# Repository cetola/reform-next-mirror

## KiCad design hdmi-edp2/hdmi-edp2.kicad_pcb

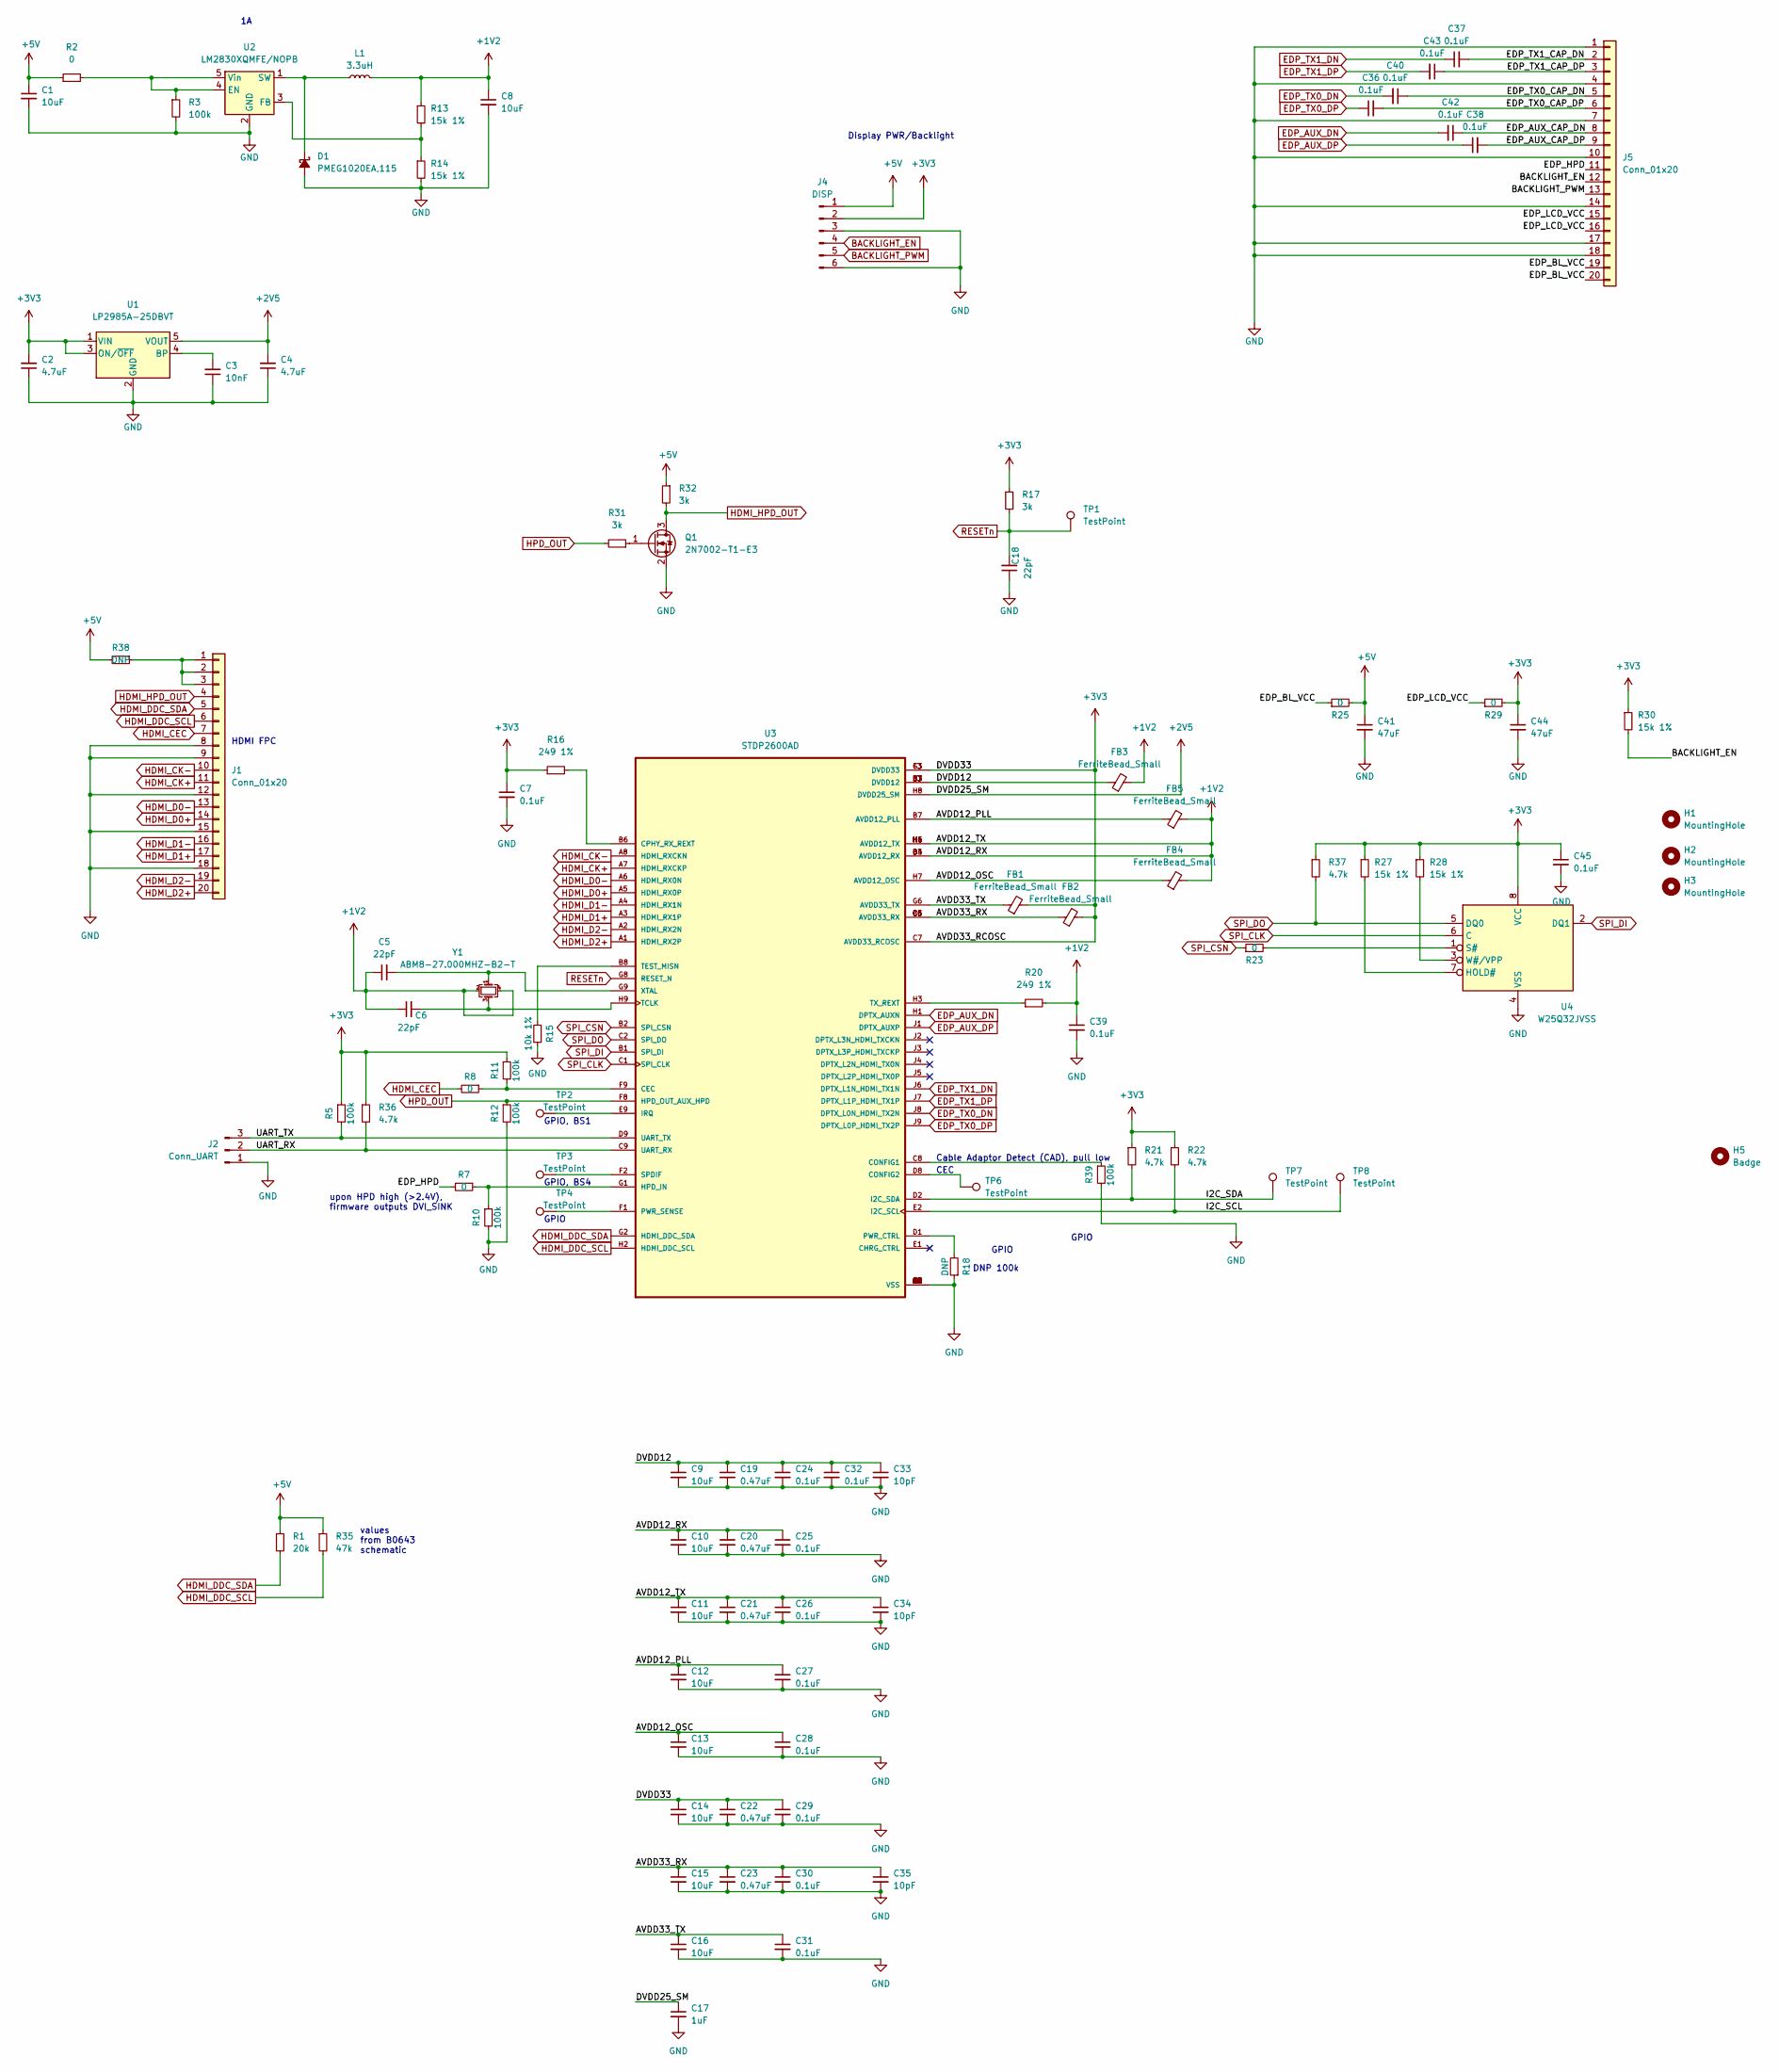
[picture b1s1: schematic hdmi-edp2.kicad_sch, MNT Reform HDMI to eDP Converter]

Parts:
C1, C8: 10uF; C_0603_1608Metric
C2, C4: 4.7uF; C_0402_1005Metric
C3: 10nF; C_0402_1005Metric
C5, C6, C18: 22pF; C_0402_1005Metric
C7, C24, C25, C26, C27, C28, C29, C30, C31, C32, C36, C37, C38, C39, C40, C42, C43, C45: 0.1uF; C_0402_1005Metric
C9, C10, C11, C12, C13, C14, C15, C16: 10uF; C_0402_1005Metric
C17: 1uF; C_0402_1005Metric
C19, C20, C21, C22, C23: 0.47uF; C_0402_1005Metric
C33, C34, C35: 10pF; C_0402_1005Metric
C41, C44: 47uF; C_0805_2012Metric
D1: PMEG1020EA,115; D_SOD-323
FB1, FB2, FB3, FB4, FB5: FerriteBead_Small; R_0603_1608Metric
H1, H2, H3: MountingHole; MountingHole_2.2mm_M2
H5: Badge; mnt-rhdp-badge-d1
J1: Conn_01x20; Hirose_FH12-20S-0.5SH_1x20-1MP_P0.50mm_Horizontal
J2: Conn_UART; PinHeader_1x03_P2.54mm_Vertical
J4: DISP; JST_SH_SM06B-SRSS-TB_1x06-1MP_P1.00mm_Horizontal
J5: Conn_01x20; JST_SH_SM20B-SRSS-TB_1x20-1MP_P1.00mm_Horizontal
L1: 3.3uH; L_1210_3225Metric
Q1: 2N7002-T1-E3; SOT-23
R1: 20k; R_0603_1608Metric
R2, R7, R8, R23, R25, R29: 0; R_0603_1608Metric
R3, R5, R10, R11, R12, R39: 100k; R_0603_1608Metric
R13, R14, R27, R28, R30: 15k 1%; R_0603_1608Metric
R15: 10k 1%; R_0603_1608Metric
R16, R20: 249 1%; R_0603_1608Metric
R17, R31, R32: 3k; R_0603_1608Metric
R18, R38: DNP; R_0603_1608Metric
R21, R22, R36, R37: 4.7k; R_0603_1608Metric
R35: 47k; R_0603_1608Metric
TP1, TP2, TP3, TP4, TP6, TP7, TP8: TestPoint; TestPoint_Pad_D1.0mm
U1: LP2985A-25DBVT; SOT-23-5
U2: LM2830XQMFE/NOPB; SOT-23-5
U3: STDP2600AD; BGA81C80P9X9_800X800X140N
U4: W25Q32JVSS; SOIC-8W_5.3x5.3mm_P1.27mm
Y1: ABM8-27.000MHZ-B2-T; Crystal_SMD_3225-4Pin_3.2x2.5mm

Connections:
+1V2: C5.1, C6.1, C8.1, C10.1, C11.1, C20.1, C21.1, C25.1, C26.1, C34.1, C39.1, FB3.2, FB4.2, FB5.2, L1.2, R13.1, R20.2, U3.B3 (AVDD12_RX), U3.B4 (AVDD12_RX), U3.H4 (AVDD12_TX), U3.H5 (AVDD12_TX), U3.H6 (AVDD12_TX), Y1.2, Y1.4
+2V5: C4.2, C17.1, U1.5 (VOUT), U3.H8 (DVDD25_SM)
+3V3: C2.2, C7.1, C14.1, C22.1, C29.1, C44.1, C45.1, FB1.2, FB2.2, J4.2, R5.1, R11.1, R16.1, R17.1, R21.1, R22.1, R27.1, R28.1, R29.2, R30.1, R36.1, R37.1, U1.1 (VIN), U1.3 (ON/~OFF), U3.C7 (AVDD33_RCOSC), U3.F3 (DVDD33), U3.G3 (DVDD33), U4.8 (VCC)
+5V: C1.1, C41.1, J4.1, R1.1, R2.1, R25.2, R32.1, R35.1, R38.2
/AVDD12_OSC: C13.1, C28.1, FB4.1, U3.H7 (AVDD12_OSC)
/AVDD12_PLL: C12.1, C27.1, FB5.1, U3.B7 (AVDD12_PLL)
/AVDD33_RX: C15.1, C23.1, C30.1, C35.1, FB2.1, U3.B5 (AVDD33_RX), U3.C5 (AVDD33_RX), U3.C6 (AVDD33_RX)
/AVDD33_TX: C16.1, C31.1, FB1.1, U3.G6 (AVDD33_TX)
/DVDD12: C9.1, C19.1, C24.1, C32.1, C33.1, FB3.1, U3.D3 (DVDD12), U3.D7 (DVDD12), U3.E3 (DVDD12), U3.E7 (DVDD12)
/EDP_AUX_CAP_DN: C42.1, J5.8
/EDP_AUX_CAP_DP: C38.2, J5.9
/EDP_BL_VCC: J5.19, J5.20, R25.1
/EDP_HPD: J5.11, R7.2
/EDP_LCD_VCC: J5.15, J5.16, R29.1
/EDP_TX0_CAP_DN: C40.1, J5.5
/EDP_TX0_CAP_DP: C36.2, J5.6
/EDP_TX1_CAP_DN: C37.2, J5.2
/EDP_TX1_CAP_DP: C43.1, J5.3
/I2C_SCL: R22.2, TP8.1, U3.E2 (I2C_SCL)
/I2C_SDA: R21.2, TP7.1, U3.D2 (I2C_SDA)
/UART_RX: J2.2, R36.2, U3.C9 (UART_RX)
/UART_TX: J2.3, R5.2, U3.D9 (UART_TX)
BACKLIGHT_EN: J4.4, J5.12, R30.2
BACKLIGHT_PWM: J4.5, J5.13
EDP_AUX_DN: C42.2, U3.H1 (DPTX_AUXN)
EDP_AUX_DP: C38.1, U3.J1 (DPTX_AUXP)
EDP_TX0_DN: C40.2, U3.J8 (DPTX_L0N_HDMI_TX2N)
EDP_TX0_DP: C36.1, U3.J9 (DPTX_L0P_HDMI_TX2P)
EDP_TX1_DN: C37.1, U3.J6 (DPTX_L1N_HDMI_TX1N)
EDP_TX1_DP: C43.2, U3.J7 (DPTX_L1P_HDMI_TX1P)
GND: C1.2, C2.1, C3.1, C4.1, C7.2, C8.2, C9.2, C10.2, C11.2, C12.2, C13.2, C14.2, C15.2, C16.2, C17.2, C18.1, C19.2, C20.2, C21.2, C22.2, C23.2, C24.2, C25.2, C26.2, C27.2, C28.2, C29.2, C30.2, C31.2, C32.2, C33.2, C34.2, C35.2, C39.2, C41.2, C44.2, C45.2, D1.2 (A), J1.8, J1.9, J1.12, J1.15, J1.18, J2.1, J4.3, J4.6, J5.1, J5.4, J5.7, J5.10, J5.14, J5.17, J5.18, Q1.2 (S), R3.2, R10.2, R12.2, R14.2, R15.1, R18.1, R39.2, U1.2 (GND), U2.2 (GND), U3.C3 (VSS), U3.C4 (VSS), U3.D4 (VSS), U3.D5 (VSS), U3.D6 (VSS), U3.E4 (VSS), U3.E5 (VSS), U3.E6 (VSS), U3.E8 (VSS), U3.F4 (VSS), U3.F5 (VSS), U3.F6 (VSS), U3.F7 (VSS), U3.G4 (VSS), U3.G5 (VSS), U3.G7 (VSS), U4.4 (VSS)
HDMI_CEC: J1.7, R8.2
HDMI_CK+: J1.11, U3.A7 (HDMI_RXCKP)
HDMI_CK-: J1.10, U3.A8 (HDMI_RXCKN)
HDMI_D0+: J1.14, U3.A5 (HDMI_RX0P)
HDMI_D0-: J1.13, U3.A6 (HDMI_RX0N)
HDMI_D1+: J1.17, U3.A3 (HDMI_RX1P)
HDMI_D1-: J1.16, U3.A4 (HDMI_RX1N)
HDMI_D2+: J1.20, U3.A1 (HDMI_RX2P)
HDMI_D2-: J1.19, U3.A2 (HDMI_RX2N)
HDMI_DDC_SCL: J1.6, R35.2, U3.H2 (HDMI_DDC_SCL)
HDMI_DDC_SDA: J1.5, R1.2, U3.G2 (HDMI_DDC_SDA)
HDMI_HPD_OUT: J1.4, Q1.3 (D), R32.2
HPD_OUT: R12.1, R31.2, U3.F8 (HPD_OUT_AUX_HPD)
unnamed: D1.1 (K), L1.1, U2.1 (SW)
unnamed: J1.1, J1.2, J1.3, R38.1
unnamed: Q1.1 (G), R31.1
unnamed: C3.2, U1.4 (BP)
unnamed: R2.2, R3.1, U2.4 (EN), U2.5 (Vin)
unnamed: R13.2, R14.1, U2.3 (FB)
unnamed: R8.1, R11.2, U3.F9 (CEC)
unnamed: R39.1, U3.C8 (CONFIG1)
unnamed: TP6.1, U3.D8 (CONFIG2)
unnamed: R16.2, U3.B6 (CPHY_RX_REXT)
unnamed: R7.1, R10.1, U3.G1 (HPD_IN)
unnamed: TP2.1, U3.E9 (IRQ)
unnamed: R18.2, U3.D1 (PWR_CTRL)
unnamed: TP4.1, U3.F1 (PWR_SENSE)
unnamed: TP3.1, U3.F2 (SPDIF)
unnamed: C6.2, U3.H9 (TCLK), Y1.3
unnamed: R15.2, U3.B8 (TEST_MISN)
unnamed: R20.1, U3.H3 (TX_REXT)
unnamed: C5.2, U3.G9 (XTAL), Y1.1
unnamed: R27.2, U4.7 (HOLD#)
unnamed: R23.2, U4.1 (S#)
unnamed: R28.2, U4.3 (W#/VPP)
RESETn: C18.2, R17.2, TP1.1, U3.G8 (RESET_N)
SPI_CLK: U3.C1 (SPI_CLK), U4.6 (C)
SPI_CSN: R23.1, U3.B2 (SPI_CSN)
SPI_DI: U3.B1 (SPI_DI), U4.2 (DQ1)
SPI_DO: R37.2, U3.C2 (SPI_DO), U4.5 (DQ0)

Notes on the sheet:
GPIO, BS4
GPIO
DNP 100k
GPIO, BS1
Display PWR/Backlight
Cable Adaptor Detect (CAD), pull low
values from B0643 schematic
CEC
upon HPD high (>2.4V), firmware outputs DVI_SINK
HDMI FPC

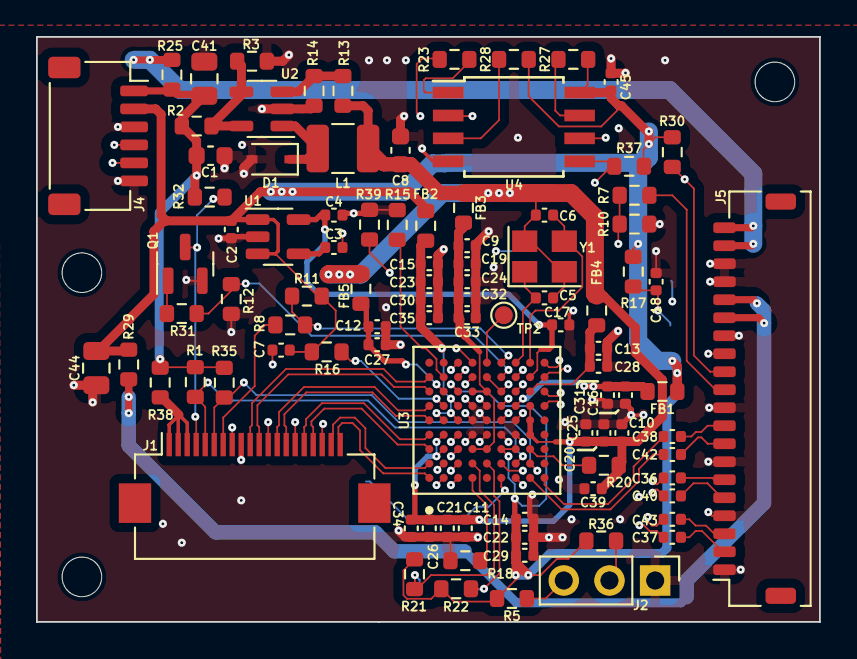
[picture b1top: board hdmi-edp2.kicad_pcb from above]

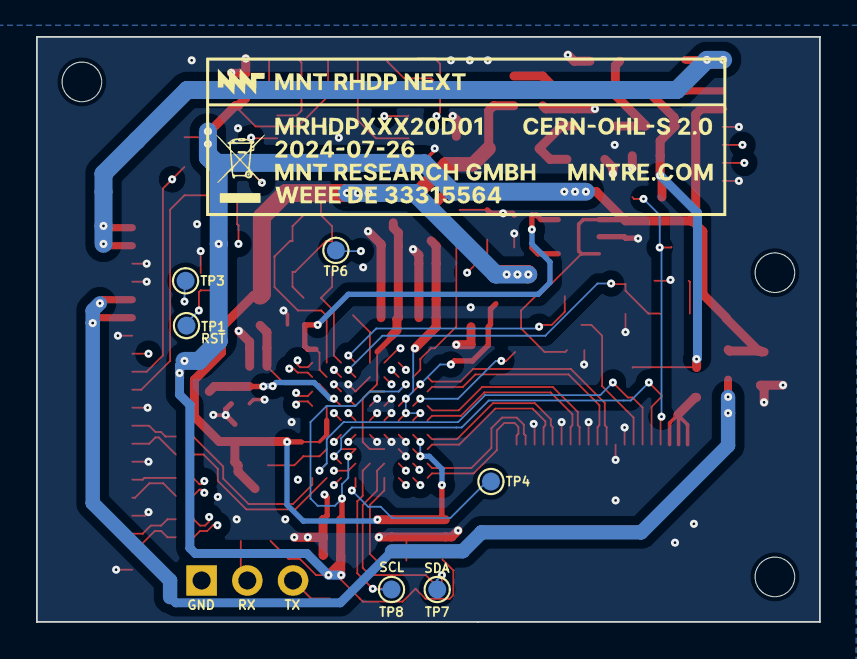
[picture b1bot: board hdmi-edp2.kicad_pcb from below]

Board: 4 copper layers, 43.5 x 32.5 mm, 104 parts (7 on the bottom side), 71 nets.

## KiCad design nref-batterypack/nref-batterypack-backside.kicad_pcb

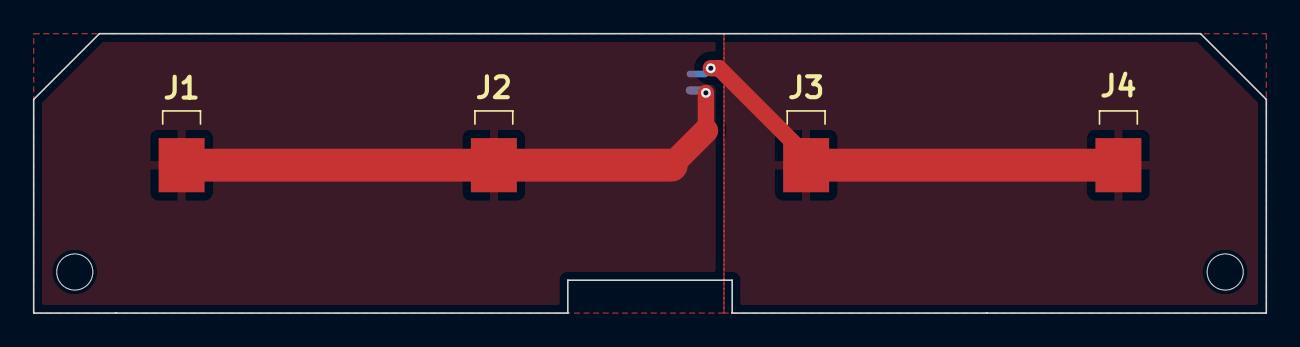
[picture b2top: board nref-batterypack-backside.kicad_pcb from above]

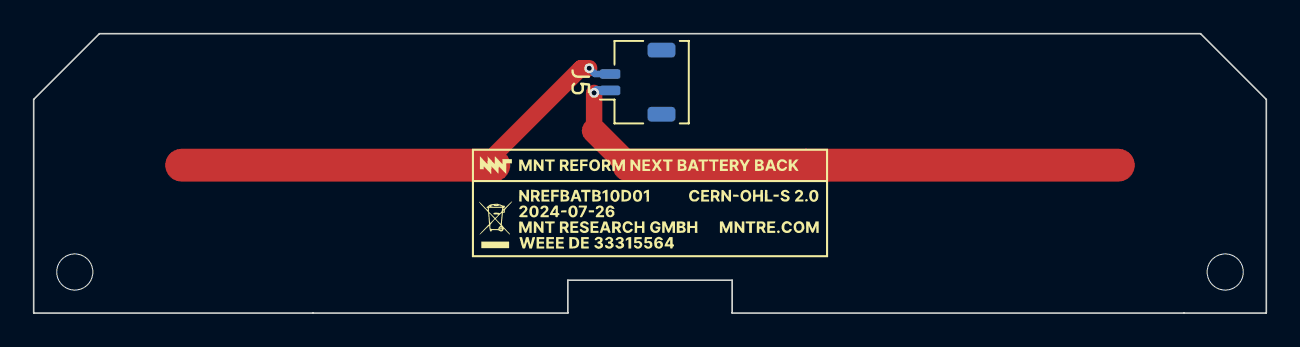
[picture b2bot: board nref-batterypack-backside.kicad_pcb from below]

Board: 2 copper layers, 75.0 x 17.0 mm, 8 parts (2 on the bottom side), 2 nets.

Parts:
H1, H2: MountingHole; MountingHole_2.2mm_M2
H3: BADGE; nref-battback-badge
J1: C1+; S713145R
J2: C2-; S713145R
J3: C3+; S713145R
J4: C4-; S713145R
J5: FRONT_CONN; JST_SHL_SM02B-SHLS-TF_1x02-1MP_P1.00mm_Horizontal

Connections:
/C1+: J1.1, J2.1, J5.1
/C3+: J3.1, J4.1, J5.2

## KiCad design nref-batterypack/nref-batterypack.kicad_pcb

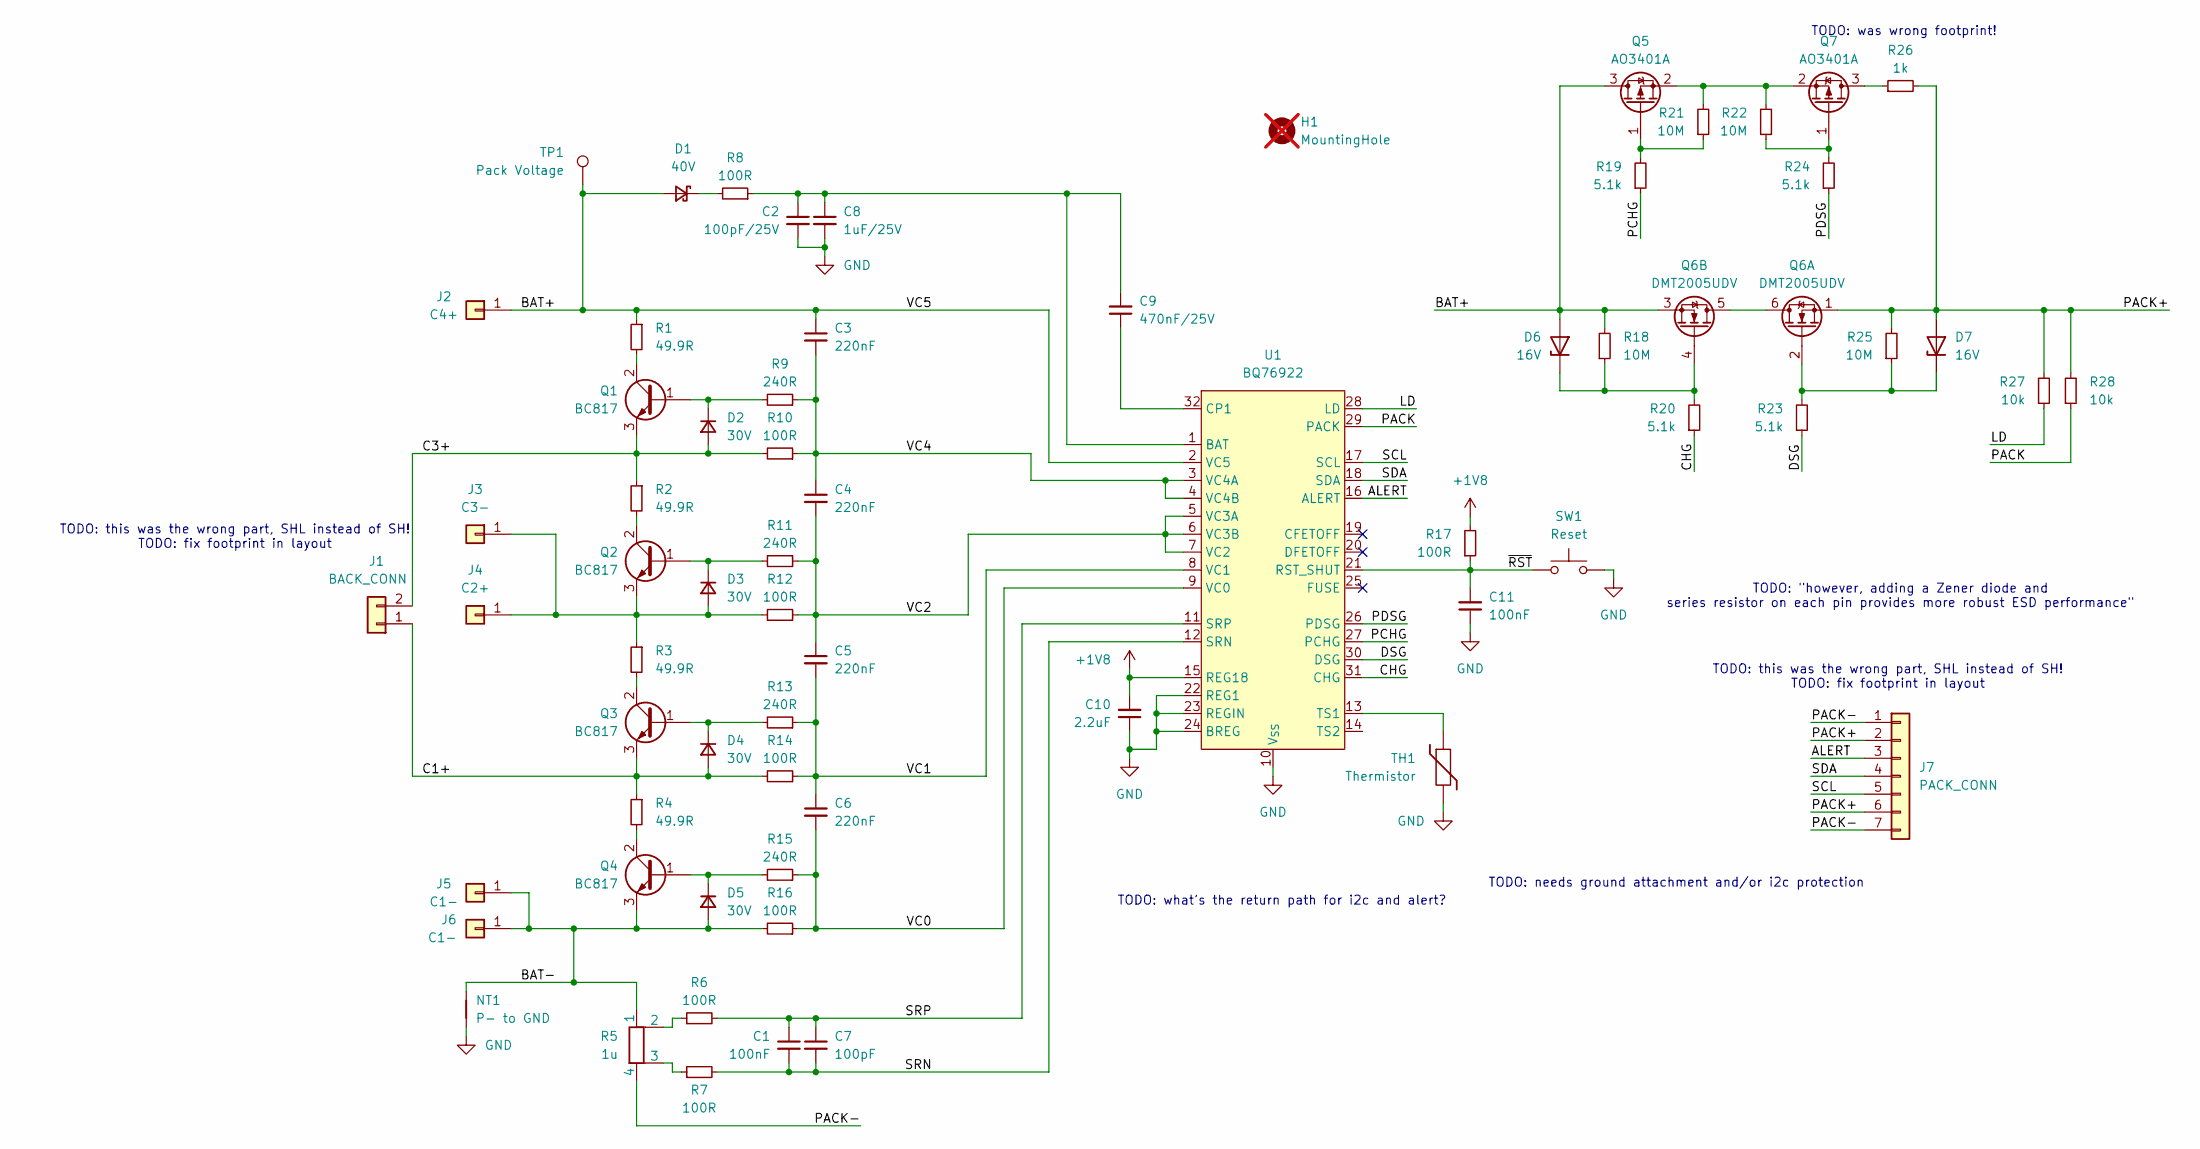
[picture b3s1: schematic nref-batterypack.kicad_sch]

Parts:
C1, C11: 100nF; C_0402_1005Metric; MPN GRM155R71C104KA88J
C2: 100pF/25V; C_0603_1608Metric; MPN GCM1885C2A101JA16D
C3, C4, C5, C6: 220nF; C_0402_1005Metric; MPN GRT155C81E224KE01D
C7: 100pF; C_0402_1005Metric; MPN GRM1555C1H101JA01D
C8: 1uF/25V; C_0603_1608Metric; MPN GRT188R61H105KE13D
C9: 470nF/25V; C_0603_1608Metric; MPN GRM188R71E474KA12D
C10: 2.2uF; C_0402_1005Metric; MPN GRM155R61E225ME15D
D1: 40V; D_SOD-323; MPN B140WS-7
D2, D3, D4, D5: 30V; D_SOD-323F; MPN PMEG3015EJ,115
D6, D7: 16V; D_SOD-323; MPN BZX384-B16,115
H1: MountingHole; MountingHole_2.2mm_M2; MPN DNP; not fitted
J1: BACK_CONN; JST_SH_SM02B-SRSS-TB_1x02-1MP_P1.00mm_Horizontal; MPN SM02B-SHLS-TF(LF)(SN)
J2: C4+; S713145R; MPN S1741-46R
J3: C3-; S713145R; MPN S1741-46R
J4: C2+; S713145R; MPN S1741-46R
J5: C1-; S713145R; MPN S1741-46R
J6: C1-; PinHeader_1x01_P1.00mm_Vertical; MPN DNP
J7: PACK_CONN; JST_SH_SM07B-SRSS-TB_1x07-1MP_P1.00mm_Horizontal; MPN SM07B-SHLS-TF(LF)(SN)
NT1: P- to GND; SolderJumper-2_P1.3mm_Bridged_RoundedPad1.0x1.5mm; MPN DNP
Q1, Q2, Q3, Q4: BC817; SOT-23; MPN BC817-25LT1G
Q5, Q7: AO3401A; SOT-23; MPN AO3401A
Q6: DMT2005UDV; Diodes_PowerDI3333-8_UXC_3.3x3.3mm_P0.65mm; MPN DMT3020LDV-7 (alternative)
R1, R2, R3, R4: 49.9R; R_1206_3216Metric; MPN RC1206FR-0749R9L
R5: 1u; R_Shunt_Vishay_WSK2512_6332Metric_T1.19mm; MPN WSK25121L000FEA
R6, R7, R8, R10, R12, R14, R16, R17: 100R; R_0402_1005Metric; MPN RC0402FR-07100RL
R9, R11, R13, R15: 240R; R_0402_1005Metric; MPN RC0402FR-07240RL
R18, R21, R22, R25: 10M; R_0402_1005Metric; MPN RC0402FR-0710ML
R19, R20, R23, R24: 5.1k; R_0402_1005Metric; MPN RC0402FR-075K1L
R26: 1k; R_1206_3216Metric
R27, R28: 10k; R_0402_1005Metric; MPN RC0402JR-0710KL
SW1: Reset; SW_SPST_PTS810; MPN PTS810 SJK 250 SMTR LFS
TH1: Thermistor; R_0603_1608Metric; MPN NTCGS163JX103DT7
TP1: Pack Voltage; TestPoint_Pad_1.5x1.5mm; MPN DNP
U1: BQ76922; Texas_RSN_WQFN-32-1EP_4x4mm_P0.4mm_EP2.8x2.8mm; MPN BQ76922

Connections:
+1V8: C10.2, R17.2, U1.15 (REG18)
/ALERT: J7.3, U1.16 (ALERT)
/BAT+: C3.1, D1.2 (A), D6.2 (A), J2.1, Q5.3 (D), Q6.3 (S), R1.1, R18.2, TP1.1, U1.2 (VC5)
/BAT-: D5.2 (A), J5.1, J6.1, NT1.2, Q4.3 (E), R5.1, R16.2
/C1+: D4.2 (A), J1.1, Q3.3 (E), R4.1, R14.2
/C3+: D2.2 (A), J1.2, Q1.3 (E), R2.1, R10.2
/CHG: R20.1, U1.31 (CHG)
/DSG: R23.1, U1.30 (DSG)
/LD: R27.1, U1.28 (LD)
/PACK: R28.1, U1.29 (PACK)
/PACK+: D7.2 (A), J7.2, J7.6, Q6.1 (S), R25.2, R26.2, R27.2, R28.2
/PACK-: J7.1, J7.7, R5.4
/PCHG: R19.1, U1.27 (PCHG)
/PDSG: R24.1, U1.26 (PDSG)
/SCL: J7.5, U1.17 (SCL)
/SDA: J7.4, U1.18 (SDA)
/SRN: C1.2, C7.2, R7.2, U1.12 (SRN)
/SRP: C1.1, C7.1, R6.2, U1.11 (SRP)
/VC0: C6.2, R15.1, R16.1, U1.9 (VC0)
/VC1: C5.2, C6.1, R13.1, R14.1, U1.8 (VC1)
/VC2: C4.2, C5.1, R11.1, R12.1, U1.5 (VC3A), U1.6 (VC3B), U1.7 (VC2)
/VC4: C3.2, C4.1, R9.1, R10.1, U1.3 (VC4A), U1.4 (VC4B)
/~RST: C11.2, R17.1, SW1.2, U1.21 (RST_SHUT)
GND: C2.2, C8.2, C10.1, C11.1, NT1.1, SW1.1, TH1.2, U1.10 (V_{SS}), U1.22 (REG1), U1.23 (REGIN), U1.24 (BREG), U1.33 (EP)
unnamed: D1.1 (K), R8.2
unnamed: D2.1 (K), Q1.1 (B), R9.2
unnamed: D3.2 (A), J3.1, J4.1, Q2.3 (E), R3.1, R12.2
unnamed: D3.1 (K), Q2.1 (B), R11.2
unnamed: D4.1 (K), Q3.1 (B), R13.2
unnamed: D5.1 (K), Q4.1 (B), R15.2
unnamed: D6.1 (K), Q6.4 (G), R18.1, R20.2
unnamed: D7.1 (K), Q6.2 (G), R23.2, R25.1
unnamed: Q1.2 (C), R1.2
unnamed: Q2.2 (C), R2.2
unnamed: Q3.2 (C), R3.2
unnamed: Q4.2 (C), R4.2
unnamed: Q5.1 (G), R19.2, R21.1
unnamed: Q5.2 (S), Q7.2 (S), R21.2, R22.2
unnamed: Q6.5 (D), Q6.6 (D)
unnamed: Q7.3 (D), R26.1
unnamed: Q7.1 (G), R22.1, R24.2
unnamed: R5.2, R6.1
unnamed: R5.3, R7.1
unnamed: C2.1, C8.1, C9.2, R8.1, U1.1 (BAT)
unnamed: C9.1, U1.32 (CP1)
unnamed: TH1.1, U1.13 (TS1)

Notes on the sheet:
TODO: what's the return path for i2c and alert?
TODO: this was the wrong part, SHL instead of SH! TODO: fix footprint in layout
TODO: "however, adding a Zener diode and series resistor on each pin provides more robust ESD performance"
TODO: needs ground attachment and/or i2c protection
TODO: was wrong footprint!

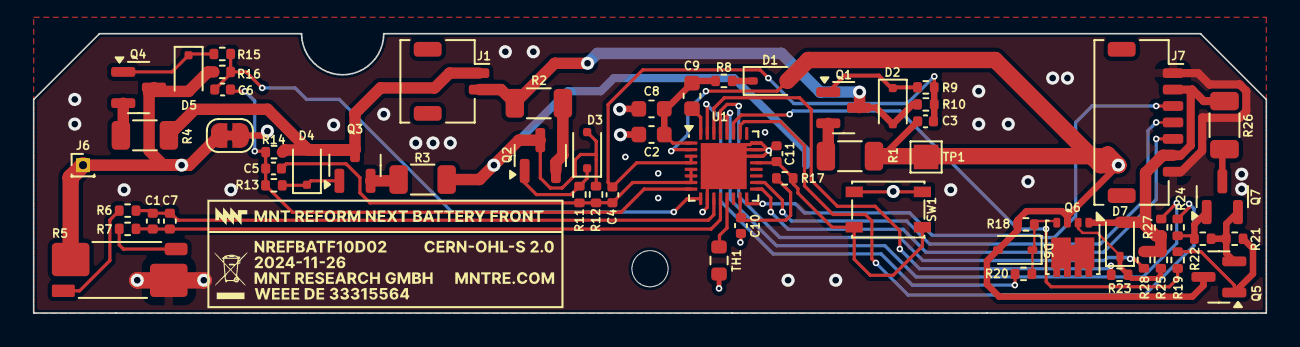
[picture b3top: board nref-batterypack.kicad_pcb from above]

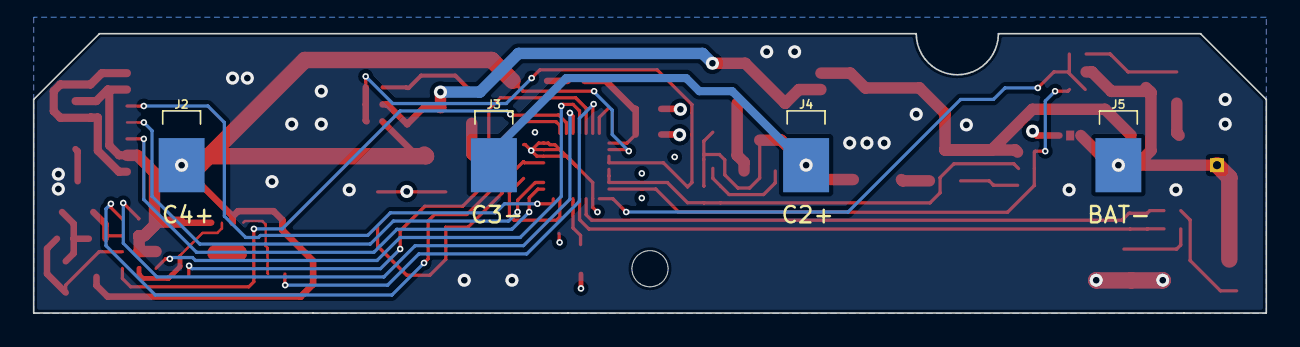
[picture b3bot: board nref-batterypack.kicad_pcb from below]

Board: 4 copper layers, 75.0 x 17.0 mm, 66 parts (4 on the bottom side), 46 nets.

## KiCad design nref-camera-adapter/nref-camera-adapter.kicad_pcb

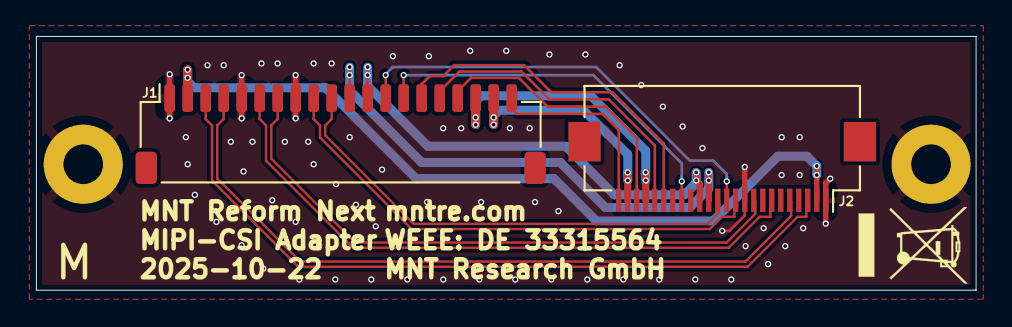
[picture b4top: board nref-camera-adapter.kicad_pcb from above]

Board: 4 copper layers, 52.2 x 14.1 mm, 4 parts (0 on the bottom side), 18 nets.

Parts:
H1, H1#2: MountingHole_Pad; MountingHole_2.2mm_M2_Pad
J1: Conn_01x20; JST_SH_SM20B-SRSS-TB_1x20-1MP_P1.00mm_Horizontal
J2: Conn_01x24; Hirose_FH12-24S-0.5SH_1x24-1MP_P0.50mm_Horizontal

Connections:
/CAM_AF_VCC: J1.2, J2.2
/CAM_AGND: J1.19, J2.23
/CAM_AVDD: J1.18, J2.21
/CAM_DOVDD: J1.11, J2.14
/CAM_DVDD: J1.12, J2.15
/CAM_MCLK: J1.13, J2.12
/CAM_MIPI_CN: J1.6, J2.7
/CAM_MIPI_CP: J1.7, J2.9
/CAM_MIPI_D0N: J1.3, J2.3
/CAM_MIPI_D0P: J1.4, J2.5
/CAM_MIPI_D1N: J1.9, J2.11
/CAM_MIPI_D1P: J1.10, J2.13
/CAM_PWDNB: J1.14, J2.17
/CAM_RST: J1.15, J2.19
/CAM_SCL: J1.16, J2.20
/CAM_SDA: J1.17, J2.22
/CAM_STROBE: J1.20, J2.24
GND: H1.1, H1#2.1, J1.1, J1.5, J1.8, J2.1, J2.10

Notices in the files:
hdmi-edp2/hdmi-edp2.kicad_sch:
License: CERN-OHL-S 2.0
